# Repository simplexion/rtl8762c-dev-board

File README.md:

# RTL8762C Development Board
Development board(s) for the Realtek [RTL8762C](https://www.realtek.com/en/products/communications-network-ics/item/rtl8762c) BLE MCU.
Please view the [product page](https://www.realmcu.com/en/Home/Product/93cc0582-3a3f-4ea8-82ea-76c6504e478a) for detailed information and documentation. 

## Features
- USB-UART for flashing and i/o
- USB-SWD for on-chip debugging

## Board Bring-Up
Please refer to the [bring-up](./bring-up.md) page for instructions.

## Variants

### RTL8762CKF

Browse the files on [KiCanvas](https://kicanvas.org/?github=https://github.com/simplexion/rtl8762c-dev-board/tree/main/source/rtl8762ckf-dev-board) - by [Stargirl Flowers](https://github.com/theacodes)

#### PDFs
- [Schematic](exports/plots//rtl8762ckf-dev-board-sch.pdf)
- [Layout](exports/plots//rtl8762ckf-dev-board-pcb.pdf)

#### On-Board
| Function | Pin  |
|----------|------|
| LED      | P4_3 |
| Button   | P1_7 |

## Directory Structure
| directory  | content                                                              |
|------------|----------------------------------------------------------------------|
| source     | KiCad project directories                                            |
| production | fabrication files (Gerber, BOM, placement)                           |
| exports    | schematic and layout plots, board 3D model and renderings            |
| datasheets | component datasheets                                                 |
| assets     | board setups, component 3D models, logos                             |
| scripts    | BOM export plugins, miscellaneous helper scripts for file conversion |
| hooks      | git hooks, for example for automatic documentation export            |

## Automation
This repository contains a Makefile that automates PDF and Gerber export.

### Requirements
Apart from [KiCad 7](#kicad-version) this requires some additional software.

The Makefile calls a Python script that makes use of [sexptdata](https://pypi.org/project/sexpdata/) to parse KiCad files.
Install [Poetry](https://python-poetry.org/) and run `poetry shell` followed by `poetry install` in the root of this repositoryto set up a virtual environment with the required package(s). To re-enter this environment, simply run `poetry shell` in the root of this repository.

For PDF export you additonally need to install [Poppler](https://poppler.freedesktop.org/).
Gerber export requires [zip](https://infozip.sourceforge.net/).

#### Nix(OS)
If you are using the Nix package manager, you can enter a development environment
with KiCad and all other software by running `nix-shell` in the root of this
repository.

### Export
To export all PDFs and production files, simply run
```shell
make
```
PDFs and production files are exported automatically when you `git commit`, if you have
[Git Hooks](#installing-git-hooks-optional) set up.

### Installing Git Hooks (optional)
The [hooks](hooks) directory contains client-side [git hooks](https://git-scm.com/book/en/v2/Customizing-Git-Git-Hooks).
Currently only the pre-commit hook is used to automatically export plots.

To enable the hooks locally, run the following in the root of the repository.
```shell
git config core.hooksPath ./hooks
```

## KiCad Version
Version information of the KiCad used to generate the files.
```
[nix-shell:~/repos/kicad-template]$ kicad-cli version --format about

Application: kicad-cli x86_64 on x86_64

Version: 7.0.1, release build

Libraries:
        wxWidgets 3.2.2
        FreeType 2.12.1
        HarfBuzz 6.0.0
        FontConfig 2.14.0
        libcurl/7.87.0 OpenSSL/3.0.8 zlib/1.2.13 brotli/1.0.9 zstd/1.5.2 libidn2/2.3.2 libssh2/1.10.0 nghttp2/1.51.0

Platform: , 64 bit, Little endian, wxBase, , wayland

Build Info:
        Date: Jan  1 1980 00:00:00
        wxWidgets: 3.2.2 (wchar_t,wx containers) GTK+ 0.0
        Boost: 1.79.0
        OCC: 7.6.2
        Curl: 7.87.0
        ngspice: 37
        Compiler: GCC 12.2.0 with C++ ABI 1017

Build settings:
        KICAD_USE_EGL=ON
        KICAD_SPICE=ON
```

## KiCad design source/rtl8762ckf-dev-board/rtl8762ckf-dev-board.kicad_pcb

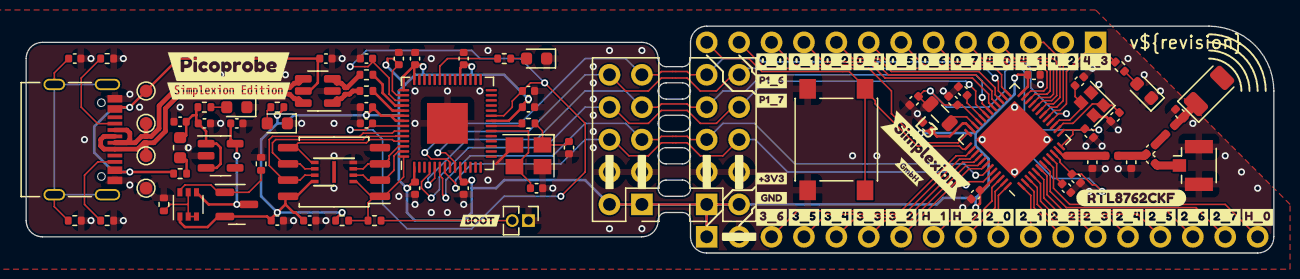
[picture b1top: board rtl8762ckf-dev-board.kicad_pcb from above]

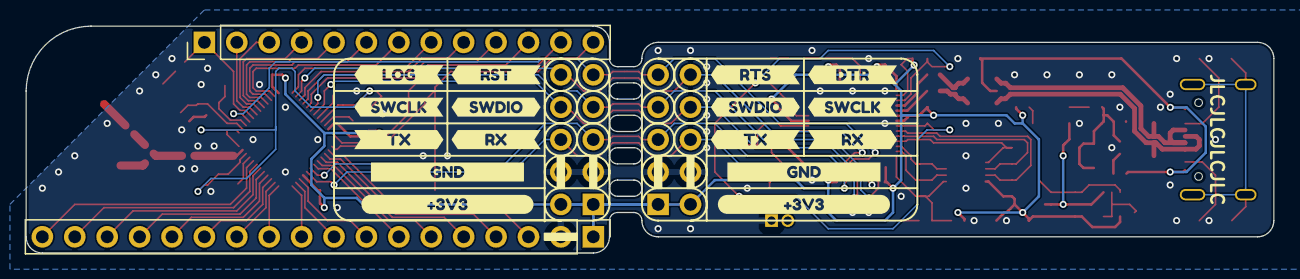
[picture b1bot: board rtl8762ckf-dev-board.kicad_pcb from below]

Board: 2 copper layers, 97.8 x 17.8 mm, 140 parts (18 on the bottom side), 85 nets.

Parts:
AE1: 2.4GHz; Johanson_2450AT18x100
C1, C2, C3, C27, C31: 1u; C_0402_1005Metric
C4, C5: 3.9p; C_0402_1005Metric
C6, C7: 22p; C_0402_1005Metric
C8: 9.1p; C_0402_1005Metric
C9, C12: C; C_0402_1005Metric
C10, C13, C14, C15, C16, C17, C18, C20, C21, C23, C26, C28, C29, C30, C32, C33, C34, C35: 100n; C_0402_1005Metric
C11, C19: 4.7u; C_0402_1005Metric
C22: 10u; C_0402_1005Metric
C24, C25: 33p; C_0402_1005Metric
D1, D2, D3, D4: LED; LED_0603_1608Metric
F1: 500mA; R_0402_1005Metric
FB1: 600Ω@100MHz; L_0603_1608Metric
J1: boot; PinHeader_1x02_P1.27mm_Vertical
J2: Conn_02x05_Odd_Even; PinHeader_2x05_P2.54mm_Vertical
J3: Conn_02x05_Odd_Even; PinSocket_2x05_P2.54mm_Vertical
J4: Conn_01x13; PinHeader_1x13_P2.54mm_Vertical
J5: Conn_01x18; PinHeader_1x18_P2.54mm_Vertical
J6: u.FL; U.FL_Hirose_U.FL-R-SMT-1_Vertical
J7: USB_C_Receptacle_USB2.0; USB_C_Receptacle_Palconn_UTC16-G
L1, L2: 2.0n; L_0402_1005Metric
L3: 2.2u; L_0805_2012Metric
NT1, NT2, NT3, NT4, NT5, NT6: NetTie_2; NetTie-2_SMD_Pad0.127mm
Q2: AO3401A; SOT-23
Q3: Dual_PNP; SOT-363_SC-70-6
R1, R2, R3, R4: 1.5k; R_0402_1005Metric
R5, R8, R11: 10k; R_0402_1005Metric
R6, R7: 5.1k; R_0402_1005Metric
R9: 47k; R_0402_1005Metric
R10, R14: 1k; R_0402_1005Metric
R12, R13: 22; R_0402_1005Metric
SW1: SW_Push; SW_Push_1P1T_NO_6x6mm_H9.5mm
TP1: GND; TestPoint_Pad_D1.0mm
TP2: VBUS; TestPoint_Pad_D1.0mm
TP3: D-; TestPoint_Pad_D1.0mm
TP4: D+; TestPoint_Pad_D1.0mm
U1: ME6211C33M5G-N; SOT-23-5
U2: RTL8762CKF; QFN-48-1EP_6x6mm_P0.4mm_EP4.3x4.3mm
U3: USBLC6-2SC6; SOT-23-6
U5: W25Q16JV; USON-8_3.0x2.0mm_P0.5mm
U6: RP2040; QFN-56-1EP_7x7mm_P0.4mm_EP3.2x3.2mm
U7: W25Q128JVS; SOIC-8_5.23x5.23mm_P1.27mm
Y1: 40MHz; Crystal_SMD_2016-4Pin_2.0x1.6mm
Y2: 12M; Crystal_SMD_3225-4Pin_3.2x2.5mm
kibuzzard-641A4D28: G***; kibuzzard-641A4D28
kibuzzard-641C73BE, kibuzzard-641C73BE#2: G***; kibuzzard-641C73BE
kibuzzard-641C73C2, kibuzzard-641C73C2#2: G***; kibuzzard-641C73C2
kibuzzard-641C73C6: G***; kibuzzard-641C73C6
kibuzzard-641C73CB: G***; kibuzzard-641C73CB
kibuzzard-641C73CF: G***; kibuzzard-641C73CF
kibuzzard-641C73D3: G***; kibuzzard-641C73D3
kibuzzard-641C73DC, kibuzzard-641C73DC#2: G***; kibuzzard-641C73DC
kibuzzard-641CA3E3: G***; kibuzzard-641CA3E3
kibuzzard-641CA3FD: G***; kibuzzard-641CA3FD
kibuzzard-641CA6AF: G***; kibuzzard-641CA6AF
kibuzzard-641CA6B4: G***; kibuzzard-641CA6B4
kibuzzard-641CA612: G***; kibuzzard-641CA612
kibuzzard-641CA619: G***; kibuzzard-641CA619
kibuzzard-641CA754: G***; kibuzzard-641CA754
kibuzzard-641CA759: G***; kibuzzard-641CA759
kibuzzard-641CCF4F: G***; kibuzzard-641CCF4F
kibuzzard-641CCF55: G***; kibuzzard-641CCF55
kibuzzard-641CD305: G***; kibuzzard-641CD305
kibuzzard-641D9DDE: G***; kibuzzard-641D9DDE
kibuzzard-642D5EF2: G***; kibuzzard-642D5EF2
kibuzzard-642D619C: G***; kibuzzard-642D619C
kibuzzard-643FF3A2: G***; kibuzzard-643FF3A2
kibuzzard-643FF3AF: G***; kibuzzard-643FF3AF
kibuzzard-643FF3B6: G***; kibuzzard-643FF3B6
kibuzzard-643FF3C1: G***; kibuzzard-643FF3C1
kibuzzard-643FF3D9: G***; kibuzzard-643FF3D9
kibuzzard-643FF3DF: G***; kibuzzard-643FF3DF
kibuzzard-643FF3E8: G***; kibuzzard-643FF3E8
kibuzzard-643FF3F7: G***; kibuzzard-643FF3F7
kibuzzard-643FF3FE: G***; kibuzzard-643FF3FE
kibuzzard-643FF35A: G***; kibuzzard-643FF35A
kibuzzard-643FF37A: G***; kibuzzard-643FF37A
kibuzzard-643FF39C: G***; kibuzzard-643FF39C
kibuzzard-643FF40B: G***; kibuzzard-643FF40B
kibuzzard-643FF41C: G***; kibuzzard-643FF41C
kibuzzard-643FF42D: G***; kibuzzard-643FF42D
kibuzzard-643FF44A: G***; kibuzzard-643FF44A
kibuzzard-643FF367: G***; kibuzzard-643FF367
kibuzzard-643FF370: G***; kibuzzard-643FF370
kibuzzard-643FF387: G***; kibuzzard-643FF387
kibuzzard-643FF393: G***; kibuzzard-643FF393
kibuzzard-643FF404: G***; kibuzzard-643FF404
kibuzzard-643FF422: G***; kibuzzard-643FF422
kibuzzard-643FF427: G***; kibuzzard-643FF427
kibuzzard-643FF432: G***; kibuzzard-643FF432
kibuzzard-643FF439: G***; kibuzzard-643FF439
kibuzzard-643FF440: G***; kibuzzard-643FF440
kibuzzard-643FF446: G***; kibuzzard-643FF446
kibuzzard-643FF486: G***; kibuzzard-643FF486

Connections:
+1V2: C14.1, C15.1, C17.1, C19.1, L3.2, U2.10 (VD12_TRX), U2.12 (VD12_PA), U2.13 (VD12_SYN), U2.33 (VDDCORE)
+3V3: C3.1, C10.2, C11.2, C13.2, C23.1, C29.1, C30.1, C32.1, C33.1, C34.1, C35.1, J2.1, J2.2, J3.1, J3.2, J5.1, NT2.1, Q2.2 (S), Q3.1 (E1), R3.2, R11.2, U2.24 (VDDIO), U2.35 (HVD), U2.45 (VBAT), U5.8 (VCC), U6.1 (IOVDD), U6.10 (IOVDD), U6.22 (IOVDD), U6.33 (IOVDD), U6.42 (IOVDD), U6.43 (ADC_AVDD), U6.48 (USB_VDD), U6.49 (IOVDD), U7.8 (VCC)
+5V: C1.1, C22.2, FB1.1, R1.2, U1.1 (VIN), U1.3 (EN)
/50ΩAntenna: C7.1, L2.1
/50ΩCond: C6.1, J6.1 (In)
/AE-feed: AE1.1 (FEED), C8.1, L2.2
/BUTTON: J4.13, SW1.2, U2.37 (P1_7)
/LED: J4.1, R4.2, U2.17 (P4_3)
/LPF: C5.1, C6.2, C7.2, L1.2
/RF: C4.1, L1.1, U2.11 (RFIO)
/RP2040/D+: R12.1, U6.47 (USB_DP)
/RP2040/D-: R13.2, U6.46 (USB_DM)
/RP2040/DVDD: C26.1, C28.1, NT1.1, U6.23 (DVDD), U6.50 (DVDD)
/RP2040/QSPI.CLK: U5.6 (CLK), U6.52 (QSPI_SCLK), U7.6 (CLK)
/RP2040/QSPI.IO0: U5.5 (DI(IO0)), U6.53 (QSPI_SD0), U7.5 (DI(IO0))
/RP2040/QSPI.IO1: U5.2 (DO(IO1)), U6.55 (QSPI_SD1), U7.2 (DO(IO1))
/RP2040/QSPI.IO2: U5.3 (IO2), U6.54 (QSPI_SD2), U7.3 (IO2)
/RP2040/QSPI.IO3: U5.7 (IO3), U6.51 (QSPI_SD3), U7.7 (IO3)
/RP2040/QSPI.~CS: R10.2, R11.1, U5.1 (~CS), U6.56 (QSPI_SS), U7.1 (~CS)
/RP2040/VREG_IN: C31.1, NT2.2, U6.44 (VREG_IN)
/RP2040/VREG_OUT: C27.1, NT1.2, U6.45 (VREG_VOUT)
/RP2040/XIN: C24.1, U6.20 (XIN), Y2.3
/RP2040/XOUT: R14.2, U6.21 (XOUT)
/RP2040/~USB_BOOT: J1.2, R10.1
/RTL8762CKF/H_0: J5.18, U2.8 (H_0/P5_0/MICBIAS)
/RTL8762CKF/H_1: J5.8, U2.46 (H_1/32K_XI)
/RTL8762CKF/H_2: J5.9, U2.47 (H_2/32K_XO)
/RTL8762CKF/P0_0: J4.11, U2.29 (P0_0)
/RTL8762CKF/P0_1: J4.10, U2.28 (P0_1)
/RTL8762CKF/P0_2: J4.9, U2.27 (P0_2)
/RTL8762CKF/P0_4: J4.8, U2.25 (P0_4)
/RTL8762CKF/P0_5: J4.7, U2.23 (P0_5)
/RTL8762CKF/P0_6: J4.6, U2.22 (P0_6)
/RTL8762CKF/P0_7: J4.5, U2.21 (P0_7)
/RTL8762CKF/P1_6: J4.12, U2.36 (P1_6)
/RTL8762CKF/P2_0: J5.10, U2.48 (P2_0/ADC_0)
/RTL8762CKF/P2_1: J5.11, U2.1 (P2_1/ADC_1)
/RTL8762CKF/P2_2: J5.12, U2.2 (P2_2/ADC_2)
/RTL8762CKF/P2_3: J5.13, U2.3 (P2_3/ADC_3)
/RTL8762CKF/P2_4: J5.14, U2.4 (P2_4/ADC_4)
/RTL8762CKF/P2_5: J5.15, U2.5 (P2_5/ADC_5)
/RTL8762CKF/P2_6: J5.16, U2.6 (P2_6/ADC_6)
/RTL8762CKF/P2_7: J5.17, U2.7 (P2_7/ADC_7)
/RTL8762CKF/P3_2: J5.7, U2.42 (P3_2)
/RTL8762CKF/P3_3: J5.6, U2.41 (P3_3)
/RTL8762CKF/P3_4: J5.5, U2.40 (P3_4)
/RTL8762CKF/P3_5: J5.4, U2.39 (P3_5)
/RTL8762CKF/P3_6: J5.3, U2.38 (P3_6)
/RTL8762CKF/P4_0: J4.4, U2.20 (P4_0)
/RTL8762CKF/P4_1: J4.3, U2.19 (P4_1)
/RTL8762CKF/P4_2: J4.2, U2.18 (P4_2)
/SWD.SWCLK: J2.8, J3.8, U2.31 (P1_1/SWDCLK), U6.4 (GPIO2)
/SWD.SWDIO: J2.7, J3.7, U2.30 (P1_0/SWDIO), U6.5 (GPIO3)
/Type-C USB 2.0/CC1: J7.A5 (CC1), R6.2
/Type-C USB 2.0/CC2: J7.B5 (CC2), R7.2
/Type-C USB 2.0/D+: J7.A6 (D+), J7.B6 (D+), TP4.1, U3.6 (IO1)
/Type-C USB 2.0/D-: J7.A7 (D-), J7.B7 (D-), TP3.1, U3.4 (IO2)
/Type-C USB 2.0/VBUS_F1: F1.2, FB1.2
/UART_{RP2040}.DTR: J2.10, NT5.1, U6.9 (GPIO7)
/UART_{RP2040}.RTS: J2.9, NT4.1, U6.8 (GPIO6)
/UART_{RP2040}.RX: J2.6, NT6.1, U6.7 (GPIO5)
/UART_{RP2040}.TX: J2.5, NT3.1, U6.6 (GPIO4)
/UART_{RTL8762C}.LOG: J3.10, NT5.2, U2.26 (P0_3/LOG_UART_TX)
/UART_{RTL8762C}.RST: J3.9, NT4.2, U2.16 (HW_RST_N)
/UART_{RTL8762C}.RX: J3.5, NT3.2, U2.43 (P3_1/HCI_UART_RX)
/UART_{RTL8762C}.TX: J3.6, NT6.2, U2.44 (P3_0/HCI_UART_TX)
/USB.D+: R12.2, U3.1 (IO1)
/USB.D-: R13.1, U3.3 (IO2)
/USB_connected: R2.2, U6.37 (GPIO25)
/ZVD1/A: C2.1, Q2.3 (D), Q3.4 (E2), U1.5 (VOUT)
Earth: C20.1, J7.S1 (SHIELD), R5.2
GND: C1.2, C2.2, C3.2, C4.2, C5.2, C8.2, C9.2, C10.1, C11.1, C12.2, C13.1, C14.2, C15.2, C16.2, C17.2, C18.2, C19.2, C20.2, C21.1, C22.1, C23.2, C24.2, C25.2, C26.2, C27.2, C28.2, C29.2, C30.2, C31.2, C32.2, C33.2, C34.2, C35.2, D1.1 (K), D2.1 (K), D3.1 (K), D4.1 (K), J1.1, J2.3, J2.4, J3.3, J3.4, J5.2, J6.2 (Ext), J7.A1 (GND), J7.A12 (GND), J7.B1 (GND), J7.B12 (GND), R5.1, R6.1, R7.1, R8.1, R9.1, SW1.1, TP1.1, U1.2 (GND), U2.49 (GND), U3.2 (GND), U5.4 (GND), U6.19 (TESTEN), U6.57 (GND), U7.4 (GND), Y1.2, Y1.4, Y2.2, Y2.4
unnamed: C25.1, R14.1, Y2.1
unnamed: D1.2 (A), R1.1
unnamed: D2.2 (A), R2.1
unnamed: D3.2 (A), R3.1
unnamed: D4.2 (A), R4.1
unnamed: Q2.1 (G), Q3.6 (C1), R9.2
unnamed: Q3.2 (B1), Q3.3 (C2), Q3.5 (B2), R8.2
unnamed: L3.1, U2.34 (LX)
unnamed: C16.1, U2.9 (VA18)
unnamed: C18.1, U2.32 (VDIGI)
unnamed: C9.1, U2.14 (XI), Y1.1
unnamed: C12.1, U2.15 (XO), Y1.3
VBUS: C21.2, F1.1, J7.A4 (VBUS), J7.A9 (VBUS), J7.B4 (VBUS), J7.B9 (VBUS), TP2.1, U3.5 (VBUS)

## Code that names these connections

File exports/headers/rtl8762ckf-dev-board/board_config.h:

/**
 * @file board_config.h
 * @author Markus Blechschmidt (blechschmidt@simplexion.de)
 * @brief Autogenerated board configuration file
 * @version 0.1
 * @date 2023-04-06
 *
 * @copyright Copyright (c) 2023 Simplexion GmbH
 *
 */

#ifndef BOARD_CONFIG_H
#define BOARD_CONFIG_H

#define BOARD_NAME ("RTL8762CKF-Dev-Board")
#define MCU_NAME ("RTL8762CKF")

#define BUTTON_PAD      (P1_7)
#define LED_PAD         (P4_3)
#define RX_PAD          (P3_1)
#define TX_PAD          (P3_0)

#endif // BOARD_CONFIG_H

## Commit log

2023-03-21 Initial commit for rtl8762c-dev-board
2023-04-05 wip with bmp
2023-04-05 implemented pico probe
2023-04-05 add bom and pos handling in automation
2023-04-05 add pinout of on-board features
2023-04-06 add net ties to uart lines
2023-04-06 implement automatic header generation
    export pinout from net list to c header
2023-04-06 remove dead code
2023-04-06 apply black
2023-04-06 fix typo
2023-04-06 add missing package
2023-04-06 make executable
2023-04-06 add headers to targets
2023-04-06 remove old code
2023-04-06 derive guard from file name; update timestring
2023-04-06 add tailing newline
2023-04-13 update bring-up
2023-04-19 correct zvd; closes #4
2023-04-19 embiggen silk screen text; #3
2023-04-19 change part number of RTL8762C power inductor; closes #2
2023-04-21 set correct PNs for R5, R8, R11; closes #5
2023-04-21 add errata
2023-04-21 add KiCanvas link
2023-04-28 moved library to submodule
2023-04-28 update license
